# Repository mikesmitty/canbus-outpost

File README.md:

# canbus-outpost

An [LCC](https://openlcb.org/) (OpenLCB) node for model railroads, built around the RP2350. One board:

- drives four servo switch machines, with frog outputs and fascia toggles
- detects RailCom decoders on four track blocks, reporting occupancy and locomotives
- drives up to 16 signal heads on an SSSB chain
- bridges the CAN bus to a host over USB GridConnect
- takes firmware upgrades over LCC

Everything is set through the node's LCC configuration, so it works with any LCC configuration tool. Signals beyond simple links need a host, such as [Interlock](https://github.com/mikesmitty/interlock).

The hardware is in `hardware/canbus-outpost/`, and a one-head signal board is in `hardware/sssb-single/` (both KiCad), each with gerbers, BOM and pick-and-place files in `production/`.

## Signal heads

> [!NOTE]
> The signal chain hasn't been run on hardware yet; so far the firmware has only passed host tests. Boards made before commit 7316e79 have no LED header, but can use a servo output instead: see [Boards without an LED header](#boards-without-an-led-header).

The board speaks [RR-CirKits](https://www.rr-cirkits.com/)' Simple Serial Signal Bus (SSSB) on the LED header: one WS2811 chip per head, daisy-chained with Futaba J servo cables. The LED header supplies 5 V through a 750 mA fuse. Head 1 is the first on the cable unless its **Chain Position** says otherwise, and every chip has to be connected for the ones after it to work, in use or not. WS2811 outputs only sink current, so heads need common-anode LEDs.

### Setting up a head

Heads start disabled, since the board can't tell which are fitted. Under **Signal Heads** in the configuration:

1. Set **Chain Speed** to match the chips' SET pin: 800 kHz when open, 400 kHz when tied to power. RR-CirKits' heads leave it open, so they run at the default of 800 kHz.
2. Set the head's **Enabled**.
3. Set the lamp on each output: **R Lamp**, **Y Lamp** and **G Lamp**, named as on an SSSB head's RGY header. The defaults are red on R, yellow on Y and green on G, which is the SSSB wiring, but any lamp can go on any output. Each output also has its own brightness.
4. Optionally, set **Lamp Fade** to Incandescent. The lamps then warm up over 150 ms and cool down over 300 ms, like ballasted bulbs, instead of switching at once. Flashing aspects fade too.
5. Optionally, set the **Flash Rate** for its flashing aspects: slow (40 a minute), medium (60, the default) or fast (90). Each output also has a **Phase**: phase B lamps light while phase A lamps are dark, so two red lamps can alternate like a crossing flasher, on one head or on two at the same rate.

To add a chip partway along the chain, set the **Chain Position** of each head after it to one more than its number, instead of setting those heads up again on their new numbers. 0, the default, means the head's own number. Two heads on one chip both show on it.

Each aspect has its own event, and only the aspects a head has lamps for are on the bus:

| Aspect | Shows |
| --- | --- |
| Dark | nothing |
| Red, Yellow, Green | that lamp |
| Flashing Red, Yellow, Green | that lamp, at the head's Flash Rate and in each output's Phase, with heads at one rate in step |
| Lunar | a lunar lamp |
| S, D, Number | the lit letters and speed number of NYC subway time signals |

A head lights one kind of lamp at a time, so a light that shows alongside another, like lunar under a red, takes a chip of its own: for example head 1 as red/yellow/green and head 2 as lunar/S/D.

### Lamps of their own

An output set to **Own Events** isn't part of the aspects. It has an On and an Off event of its own, under **Own Events** at the end of **Signal Heads**, and lights at its brightness, fading if the head fades. Use it for panel lights, building lights, or lamps that must light together on one chip. Its events are on the bus while its head is enabled, and it starts out dark. A head whose outputs are all Own Events or None has no aspects on the bus, not even Dark.

### Boards without an LED header

On boards made before the LED header, a servo output can carry the chain:

1. Buffer the data line to 5 V. The servo outputs come straight from the RP2350 at 3.3 V, short of the 3.5 V a WS2811 on 5 V needs for a high. A 74AHCT125-family buffer powered from the servo header's 5 V does it, followed by a 33 Ω resistor as on the LED header. MOSFET level shifters of the kind sold for I2C are too slow at 800 kHz. The [head board](#head-board) can carry the buffer itself.
2. Set **Connected To** under **Signal Heads** to that servo. Its switch machine is then out of use, as if disabled, and the other three work as usual.

The servo header's 5 V comes straight from the board's regulator, without the LED header's 750 mA fuse, so put a fuse in the adapter.

### Head board

`hardware/sssb-single/` is a board for one head: a WS2811 with IN and OUT headers for the chain and an RGY header for a common-anode head. IN and OUT are S, +, − in servo cable order, the same as the LED header, and RGY is 5V, R, G, Y. SET is open, so it runs at 800 kHz. It hasn't been built yet.

It's assembled one of two ways:

- **R1 fitted** (the default): for a head fed by the LED header or another head.
- **U1 and C2 fitted, R1 left off**: the head buffers its own input to 5 V, so it can be the first head on a servo output. U1 is a 74AHCT1G125.

Never fit U1 and R1 together: U1's 5 V output would drive back into the pin feeding the chain. The board has no fuse, so on a servo output put one in the cable.

### Checking the chain

**Signal Test**, at the end of **Signal Heads**, has a Start and a Stop event. From Start until Stop, every chip on the chain, set up or not, lights red, yellow and green in turn and then none, a second each (outputs R, Y and G, as SSSB heads are wired). The heads still follow their events meanwhile, and go back to their aspects at Stop. Each node has its own pair by default; give every node the same pair to test all the chains on the layout at once.

On the USB console, `lights test` does the same until `lights test` again, and `lights <chip> <r> <y> <g>` sets one chip's red, yellow and green directly until the application next updates that chip, ending any test. Chips count from 0 here.

### What to expect from a host

The node has no signal logic. A head shows the last aspect event it received.

- **Simple cases need no host.** An aspect can use the same event ID as a single input, like a turnout's feedback event. Anything that depends on occupancy, routes or the next signal needs a host to decide and send the aspects.
- **A signal with two heads takes one event per head.** Each aspect holds one event ID, so a single event for a whole indication, like red over lunar, only works on a one-chip signal. Two indications that both show red would need two IDs on the same aspect.
- **Heads that always match can share event IDs.** Share all of them or none, or a host that reads a head's state back can mistake one head's aspect for the other's.
- **A reset puts a head on its Power-On Aspect** until the host sends it another.
- **A head doesn't announce changes.** It answers an event identify with the aspect it's showing.

## Building

You'll need CMake, Ninja, `arm-none-eabi-gcc` and `picotool`, the Pico SDK 2.2.0 at `~/.pico-sdk/sdk/2.2.0/`, and FreeRTOS-Kernel at `FREERTOS_KERNEL_PATH`.

```bash
make                  # build the firmware
make flash            # build and load it with picotool
make test             # run the host tests; no hardware needed
```

Once per board, in BOOTSEL mode, install the A/B partition table that LCC firmware upgrades need. It keeps the saved configuration and node ID in the top 64 KB of flash:

```bash
make partition-table
```

A running board goes into BOOTSEL mode without its button through `picotool reboot -f -u` over USB.

Flash with picotool rather than SWD, since loading over SWD replaces the partition table.

Boards set up before the top 64 KB was kept clear have partition B running up to the last 16 KB. They keep working and keep their configuration, but can save only 4 KB of it until they get the new table, which the firmware reports on the debug log at startup. Installing it moves the configuration across on its next save.

## Node ID

Set each board's ID from your OpenLCB-assigned range on the USB console:

```
nodeid 05.01.01.01.12.34
```

Until then the board uses a locally allocated stand-in with an `0A` prefix, made from the chip's device ID.

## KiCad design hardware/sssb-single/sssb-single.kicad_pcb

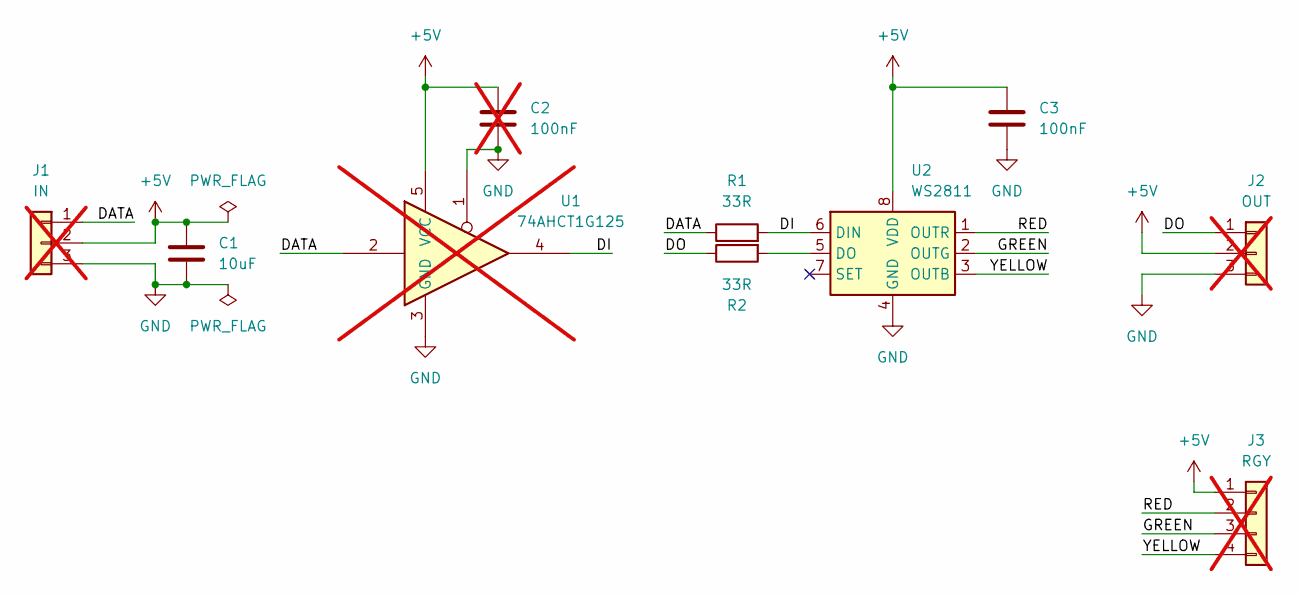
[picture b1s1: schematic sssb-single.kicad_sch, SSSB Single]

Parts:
C1: 10uF; C_0805_2012Metric; LCSC C15850
C2: 100nF; C_0805_2012Metric; LCSC C49678; not fitted
C3: 100nF; C_0805_2012Metric; LCSC C49678
J1: IN; PinHeader_1x03_P2.54mm_Vertical; not fitted
J2: OUT; PinHeader_1x03_P2.54mm_Vertical; not fitted
J3: RGY; PinHeader_1x04_P2.54mm_Vertical; not fitted
R1, R2: 33R; R_0805_2012Metric; LCSC C17634
U1: 74AHCT1G125; SOT-23-5; not fitted
U2: WS2811; SOIC-8_3.9x4.9mm_P1.27mm; LCSC C114581

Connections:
+5V: C1.1, C2.1, C3.1, J1.2, J2.2, J3.1, U1.5 (VCC), U2.8 (VDD)
/DATA: J1.1, R1.1, U1.2
/DI: R1.2, U1.4, U2.6 (DIN)
/DO: J2.1, R2.1
/GREEN: J3.3, U2.2 (OUTG)
/RED: J3.2, U2.1 (OUTR)
/YELLOW: J3.4, U2.3 (OUTB)
GND: C1.2, C2.2, C3.2, J1.3, J2.3, U1.1, U1.3 (GND), U2.4 (GND)
unnamed: R2.2, U2.5 (DO)

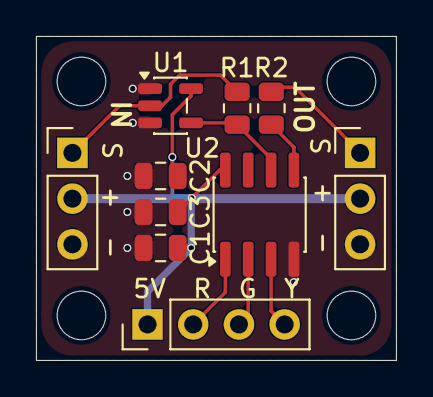
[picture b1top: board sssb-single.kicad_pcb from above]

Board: 2 copper layers, 20.0 x 18.0 mm, 10 parts (0 on the bottom side), 9 nets.

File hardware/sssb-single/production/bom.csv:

Comment,Designator,Footprint,LCSC
100nF,C3,Capacitor_SMD:C_0805_2012Metric,C49678
33R,"R1,R2",Resistor_SMD:R_0805_2012Metric,C17634
10uF,C1,Capacitor_SMD:C_0805_2012Metric,C15850
WS2811,U2,Package_SO:SOIC-8_3.9x4.9mm_P1.27mm,C114581

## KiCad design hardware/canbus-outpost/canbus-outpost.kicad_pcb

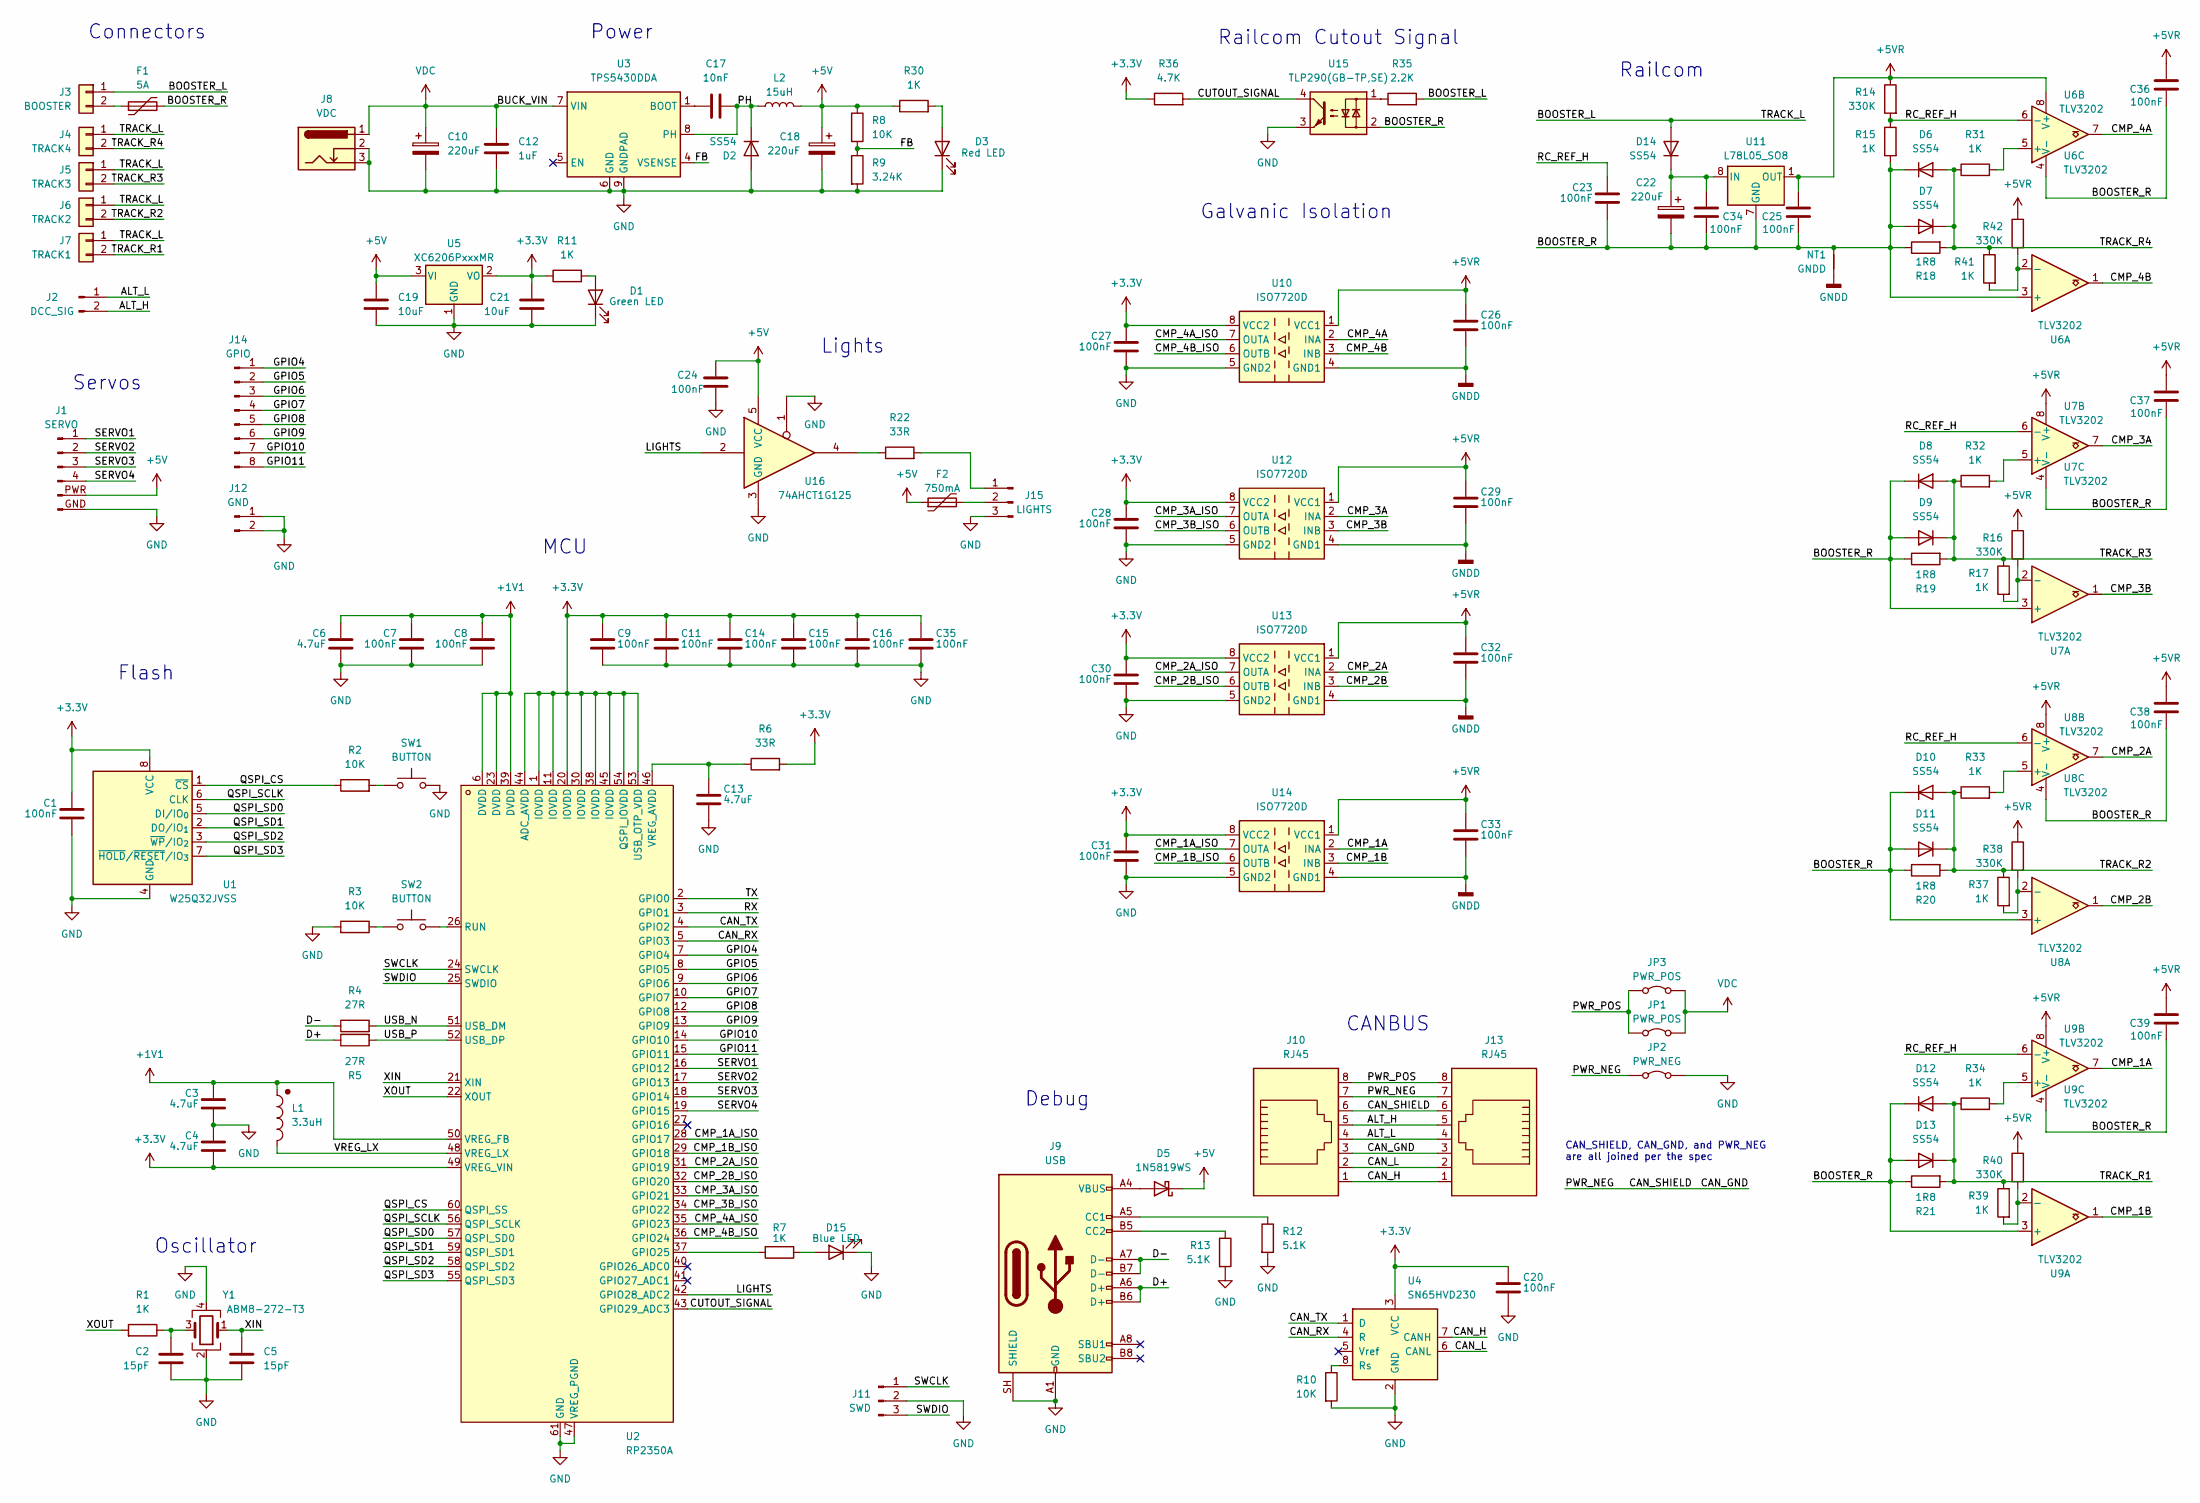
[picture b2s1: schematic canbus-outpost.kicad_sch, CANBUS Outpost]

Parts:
C1, C7, C8, C9, C11, C14, C15, C16, C20, C23, C24, C25, C26, C27, C28, C29, C30, C31, C32, C33, C34, C35, C36, C37, C38, C39: 100nF; C_0402_1005Metric; LCSC C1525
C2, C5: 15pF; C_0402_1005Metric; LCSC C1548
C3, C4: 4.7uF; C_0402_1005Metric_small_pads; LCSC C23733
C6, C13: 4.7uF; C_0402_1005Metric; LCSC C23733
C10, C18, C22: 220uF; CP_Elec_6.3x7.7; LCSC C7471881
C12: 1uF; C_0603_1608Metric; LCSC C15849
C17: 10nF; C_0402_1005Metric; LCSC C15195
C19, C21: 10uF; C_0805_2012Metric; LCSC C15850
D1: Green LED; LED_0603_1608Metric; LCSC C965804
D2, D6, D7, D8, D9, D10, D11, D12, D13, D14: SS54; D_SMA; LCSC C22452
D3: Red LED; LED_0603_1608Metric; LCSC C2286
D5: 1N5819WS; D_SOD-323; LCSC C191023
D15: Blue LED; LED_0603_1608Metric; LCSC C965807
F1: 5A; Fuse_2920_7451Metric; LCSC C20539728
F2: 750mA; Fuse_1206_3216Metric; LCSC C2830242
J1: SERVO; ServoHeader_3x04_2.54mm
J2: DCC_SIG; JST_XH_S2B-XH-A_1x02_P2.50mm_Horizontal
J3: BOOSTER; PhoenixContact_MC_1,5_2-G-3.5_1x02_P3.50mm_Horizontal
J4: TRACK4; PhoenixContact_MC_1,5_2-G-3.5_1x02_P3.50mm_Horizontal
J5: TRACK3; PhoenixContact_MC_1,5_2-G-3.5_1x02_P3.50mm_Horizontal
J6: TRACK2; PhoenixContact_MC_1,5_2-G-3.5_1x02_P3.50mm_Horizontal
J7: TRACK1; PhoenixContact_MC_1,5_2-G-3.5_1x02_P3.50mm_Horizontal
J8: VDC; BarrelJack_Wuerth_694106106102_2.0x5.5mm; LCSC C319134
J9: USB; USB_C_Receptacle_GCT_USB4115-03-C; LCSC C720628
J10, J13: RJ45; RJ45_Amphenol_54602-x08_Horizontal; LCSC C3000197
J11: SWD; PinHeader_1x03_P2.54mm_Vertical
J12: GND; PinHeader_1x02_P2.54mm_Vertical
J14: GPIO; PinHeader_1x08_P2.54mm_Vertical
J15: LIGHTS; PinHeader_1x03_P2.54mm_Vertical
JP1: PWR_POS; PinHeader_1x02_P2.54mm_Vertical
JP2: PWR_NEG; SolderJumper-2_P1.3mm_Bridged_Pad1.0x1.5mm
JP3: PWR_POS; SolderJumper-2_P1.3mm_Bridged_Pad1.0x1.5mm
L1: 3.3uH; L_pol_2016; LCSC C42411119
L2: 15uH; L_Changjiang_FXL0630; LCSC C177243
NT1: GNDD; NetTie-2_SMD_Pad0.5mm
R1, R7, R11, R15, R17, R30, R31, R32, R33, R34, R37, R39, R41: 1K; R_0402_1005Metric; LCSC C11702
R2, R3, R8, R10: 10K; R_0402_1005Metric; LCSC C25744
R4, R5: 27R; R_0402_1005Metric; LCSC C25100
R6, R22: 33R; R_0402_1005Metric; LCSC C25105
R9: 3.24K; R_0402_1005Metric; LCSC C11457
R12, R13: 5.1K; R_0402_1005Metric; LCSC C25905
R14, R16, R38, R40, R42: 330K; R_0402_1005Metric; LCSC C25778
R18, R19, R20, R21: 1R8; R_1206_3216Metric; LCSC C15545
R35: 2.2K; R_1206_3216Metric; LCSC C17948
R36: 4.7K; R_0402_1005Metric; LCSC C25900
SW1, SW2: BUTTON; SW_SPST_PTS810; LCSC C139797
U1: W25Q32JVSS; SOIC-8_5.3x5.3mm_P1.27mm; LCSC C179173
U2: RP2350A; QFN-60-1EP_7x7mm_P0.4mm_EP3.4x3.4mm; LCSC C42411118
U3: TPS5430DDA; TI_SO-PowerPAD-8_ThermalVias; LCSC C9864
U4: SN65HVD230; SOIC-8_3.9x4.9mm_P1.27mm; LCSC C12084
U5: XC6206PxxxMR; SOT-23-3; LCSC C5446
U6, U7, U8, U9: TLV3202; SOIC-8_3.9x4.9mm_P1.27mm; LCSC C129325
U10, U12, U13, U14: ISO7720D; SOIC-8_3.9x4.9mm_P1.27mm; LCSC C486037
U11: L78L05_SO8; SOIC-8_3.9x4.9mm_P1.27mm; LCSC C7543
U15: TLP290(GB-TP,SE); SOIC-4_4.55x2.6mm_P1.27mm; LCSC C73839
U16: 74AHCT1G125; SOT-23-5; LCSC C7484
Y1: ABM8-272-T3; Crystal_SMD_3225-4Pin_3.2x2.5mm; LCSC C20625731

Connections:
+1V1: C3.1, C6.1, C7.1, C8.1, L1.1, U2.6 (DVDD), U2.23 (DVDD), U2.39 (DVDD), U2.50 (VREG_FB)
+3.3V: C1.1, C4.2, C9.1, C11.1, C14.1, C15.1, C16.1, C20.1, C21.1, C27.1, C28.1, C30.1, C31.1, C35.1, R6.2, R11.1, R36.1, U1.8 (VCC), U2.1 (IOVDD), U2.11 (IOVDD), U2.20 (IOVDD), U2.30 (IOVDD), U2.38 (IOVDD), U2.44 (ADC_AVDD), U2.45 (IOVDD), U2.49 (VREG_VIN), U2.53 (USB_OTP_VDD), U2.54 (QSPI_IOVDD), U4.3 (VCC), U5.2 (VO), U10.8 (VCC2), U12.8 (VCC2), U13.8 (VCC2), U14.8 (VCC2)
+5V: C18.1, C19.1, C24.1, D5.1 (K), F2.1, J1.PWR (Pin_5), L2.2, R8.1, R30.1, U5.3 (VI), U16.5 (VCC)
+5VR: C25.1, C26.1, C29.1, C32.1, C33.1, C36.1, C37.1, C38.1, C39.1, R14.1, R16.1, R38.1, R40.1, R42.1, U6.8 (V+), U7.8 (V+), U8.8 (V+), U9.8 (V+), U10.1 (VCC1), U11.1 (OUT), U12.1 (VCC1), U13.1 (VCC1), U14.1 (VCC1)
/ALT_H: J2.2, J10.5, J13.5
/ALT_L: J2.1, J10.4, J13.4
/BOOSTER_L: D14.2 (A), J3.1, J4.1, J5.1, J6.1, J7.1, R35.2
/BOOSTER_R: C22.2, C23.2, C25.2, C34.2, C36.2, C37.2, C38.2, C39.2, D6.1 (K), D7.2 (A), D8.1 (K), D9.2 (A), D10.1 (K), D11.2 (A), D12.1 (K), D13.2 (A), F1.2, NT1.2, R15.2, R18.1, R19.1, R20.1, R21.1, U6.3 (+), U6.4 (V-), U7.3 (+), U7.4 (V-), U8.3 (+), U8.4 (V-), U9.3 (+), U9.4 (V-), U11.2 (GND), U11.3 (GND), U11.6 (GND), U11.7 (GND), U15.2
/CAN_GND: J10.3, J10.6, J10.7, J13.3, J13.6, J13.7, JP2.1 (A)
/CAN_H: J10.1, J13.1, U4.7 (CANH)
/CAN_L: J10.2, J13.2, U4.6 (CANL)
/CAN_RX: U2.5 (GPIO3), U4.4 (R)
/CAN_TX: U2.4 (GPIO2), U4.1 (D)
/CMP_1A: U9.7, U14.2 (INA)
/CMP_1A_ISO: U2.28 (GPIO17), U14.7 (OUTA)
/CMP_1B: U9.1, U14.3 (INB)
/CMP_1B_ISO: U2.29 (GPIO18), U14.6 (OUTB)
/CMP_2A: U8.7, U13.2 (INA)
/CMP_2A_ISO: U2.31 (GPIO19), U13.7 (OUTA)
/CMP_2B: U8.1, U13.3 (INB)
/CMP_2B_ISO: U2.32 (GPIO20), U13.6 (OUTB)
/CMP_3A: U7.7, U12.2 (INA)
/CMP_3A_ISO: U2.33 (GPIO21), U12.7 (OUTA)
/CMP_3B: U7.1, U12.3 (INB)
/CMP_3B_ISO: U2.34 (GPIO22), U12.6 (OUTB)
/CMP_4A: U6.7, U10.2 (INA)
/CMP_4A_ISO: U2.35 (GPIO23), U10.7 (OUTA)
/CMP_4B: U6.1, U10.3 (INB)
/CMP_4B_ISO: U2.36 (GPIO24), U10.6 (OUTB)
/CUTOUT_SIGNAL: R36.2, U2.43 (GPIO29_ADC3), U15.4
/D+: J9.A6 (D+), J9.B6 (D+), R5.1
/D-: J9.A7 (D-), J9.B7 (D-), R4.1
/FB: R8.2, R9.1, U3.4 (VSENSE)
/GPIO4: J14.1, U2.7 (GPIO4)
/GPIO5: J14.2, U2.8 (GPIO5)
/GPIO6: J14.3, U2.9 (GPIO6)
/GPIO7: J14.4, U2.10 (GPIO7)
/GPIO8: J14.5, U2.12 (GPIO8)
/GPIO9: J14.6, U2.13 (GPIO9)
/GPIO10: J14.7, U2.14 (GPIO10)
/GPIO11: J14.8, U2.15 (GPIO11)
/LIGHTS: U2.42 (GPIO28_ADC2), U16.2
/PH: C17.2, D2.1 (K), L2.1, U3.8 (PH)
/PWR_POS: J10.8, J13.8, JP1.1 (A), JP3.1 (A)
/QSPI_CS: R2.1, U1.1 (~CS), U2.60 (QSPI_SS)
/QSPI_SCLK: U1.6 (CLK), U2.56 (QSPI_SCLK)
/QSPI_SD0: U1.5 (DI/IO_{0}), U2.57 (QSPI_SD0)
/QSPI_SD1: U1.2 (DO/IO_{1}), U2.59 (QSPI_SD1)
/QSPI_SD2: U1.3 (~WP/IO_{2}), U2.58 (QSPI_SD2)
/QSPI_SD3: U1.7 (~HOLD/~RESET/IO_{3}), U2.55 (QSPI_SD3)
/RC_REF_H: C23.1, R14.2, R15.1, U6.6 (-), U7.6 (-), U8.6 (-), U9.6 (-)
/RX: U2.3 (GPIO1)
/SERVO1: J1.1, U2.16 (GPIO12)
/SERVO2: J1.2, U2.17 (GPIO13)
/SERVO3: J1.3, U2.18 (GPIO14)
/SERVO4: J1.4, U2.19 (GPIO15)
/SWCLK: J11.1, U2.24 (SWCLK)
/SWDIO: J11.3, U2.25 (SWDIO)
/TRACK_R1: D12.2 (A), D13.1 (K), J7.2, R21.2, R34.1, R39.1
/TRACK_R2: D10.2 (A), D11.1 (K), J6.2, R20.2, R33.1, R37.1
/TRACK_R3: D8.2 (A), D9.1 (K), J5.2, R17.1, R19.2, R32.1
/TRACK_R4: D6.2 (A), D7.1 (K), J4.2, R18.2, R31.1, R41.1
/TX: U2.2 (GPIO0)
/USB_N: R4.2, U2.51 (USB_DM)
/USB_P: R5.2, U2.52 (USB_DP)
/VREG_LX: L1.2, U2.48 (VREG_LX)
/XIN: C5.1, U2.21 (XIN), Y1.1
/XOUT: R1.2, U2.22 (XOUT)
GND: C1.2, C2.2, C3.2, C4.1, C5.2, C6.2, C7.2, C8.2, C9.2, C10.2, C11.2, C12.2, C13.2, C14.2, C15.2, C16.2, C18.2, C19.2, C20.2, C21.2, C24.2, C27.2, C28.2, C30.2, C31.2, C35.2, D1.1 (K), D2.2 (A), D3.1 (K), D15.1 (K), J1.GND (Pin_6), J8.2, J8.3, J9.A1 (GND), J9.A12 (GND), J9.B1 (GND), J9.B12 (GND), J9.SH (SHIELD), J11.2, J12.1, J12.2, J15.3, JP2.2 (B), R3.2, R9.2, R10.2, R12.2, R13.2, SW1.2, U1.4 (GND), U2.47 (VREG_PGND), U2.61 (GND), U3.6 (GND), U3.9 (GNDPAD), U4.2 (GND), U5.1 (GND), U10.5 (GND2), U12.5 (GND2), U13.5 (GND2), U14.5 (GND2), U15.3, U16.1, U16.3 (GND), Y1.2, Y1.4
GNDD: C26.2, C29.2, C32.2, C33.2, NT1.1, U10.4 (GND1), U12.4 (GND1), U13.4 (GND1), U14.4 (GND1)
unnamed: C2.1, R1.1, Y1.3
unnamed: D1.2 (A), R11.2
unnamed: D3.2 (A), R30.2
unnamed: D5.2 (A), J9.A4 (VBUS), J9.A9 (VBUS), J9.B4 (VBUS), J9.B9 (VBUS)
unnamed: C22.1, C34.1, D14.1 (K), U11.8 (IN)
unnamed: D15.2 (A), R7.1
unnamed: F1.1, J3.2
unnamed: J9.A5 (CC1), R12.1
unnamed: J9.B5 (CC2), R13.1
unnamed: J15.1, R22.2
unnamed: F2.2, J15.2
unnamed: R2.2, SW1.1
unnamed: R3.1, SW2.2
unnamed: R22.1, U16.4
unnamed: R35.1, U15.1
unnamed: R7.2, U2.37 (GPIO25)
unnamed: SW2.1, U2.26 (RUN)
unnamed: C13.1, R6.1, U2.46 (VREG_AVDD)
unnamed: C17.1, U3.1 (BOOT)
unnamed: R10.1, U4.8 (Rs)
unnamed: R41.2, R42.2, U6.2 (-)
unnamed: R31.2, U6.5 (+)
unnamed: R16.2, R17.2, U7.2 (-)
unnamed: R32.2, U7.5 (+)
unnamed: R37.2, R38.2, U8.2 (-)
unnamed: R33.2, U8.5 (+)
unnamed: R39.2, R40.2, U9.2 (-)
unnamed: R34.2, U9.5 (+)
VDC: C10.1, C12.1, J8.1, JP1.2 (B), JP3.2 (B), U3.7 (VIN)

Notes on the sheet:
Oscillator
Lights
Railcom
CAN_SHIELD, CAN_GND, and PWR_NEG are all joined per the spec
Galvanic Isolation
MCU
Railcom Cutout Signal
Debug
Servos
Flash
Connectors
Power
CANBUS

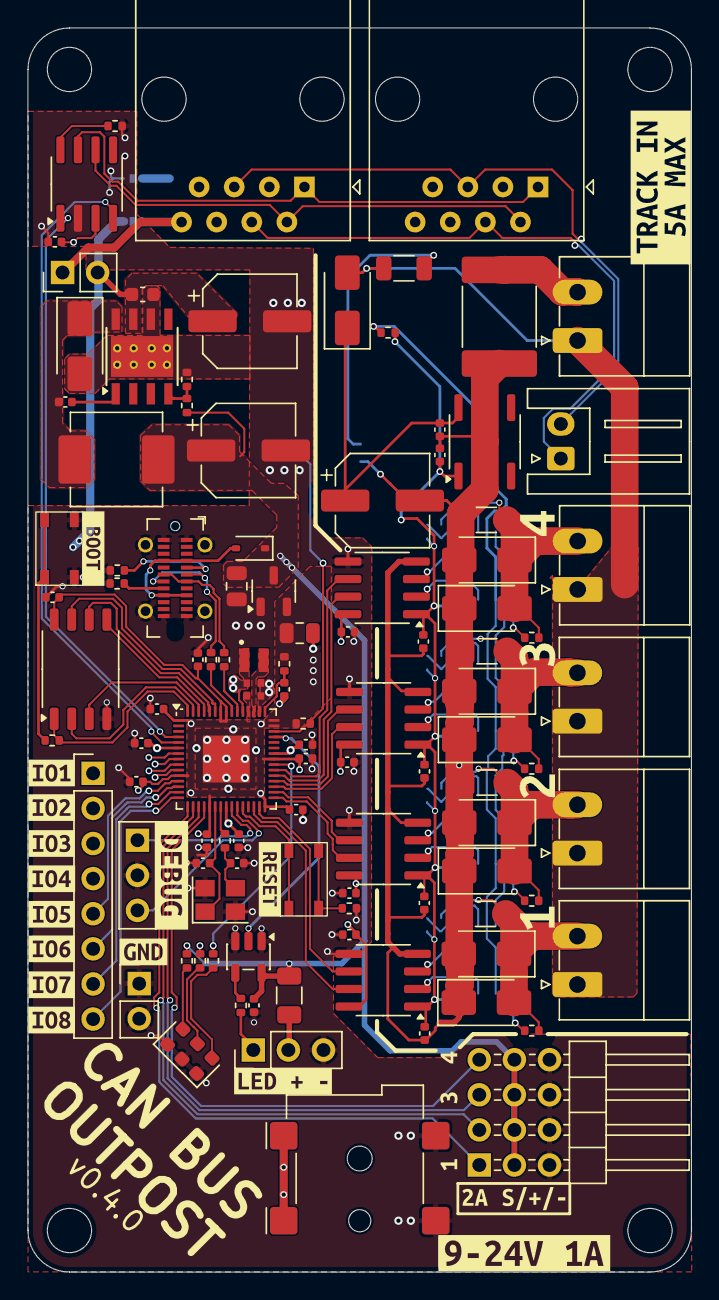
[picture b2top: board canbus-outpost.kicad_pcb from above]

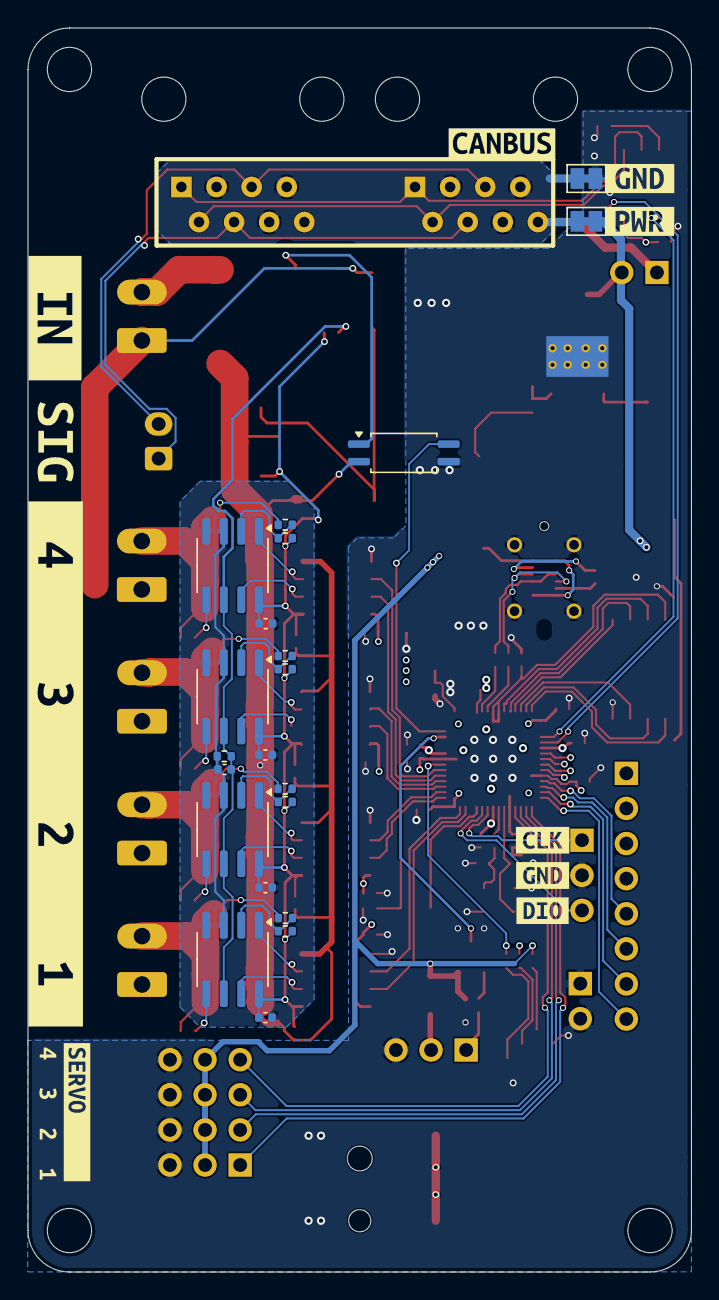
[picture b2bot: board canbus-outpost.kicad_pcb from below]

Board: 4 copper layers, 48.0 x 90.0 mm, 162 parts (32 on the bottom side), 97 nets.

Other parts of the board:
kibuzzard-6AE53D03: G***; kibuzzard-6AE53D03
kibuzzard-6AE558B7: G***; kibuzzard-6AE558B7
kibuzzard-69DC4DF3: G***; kibuzzard-69DC4DF3
kibuzzard-69DC4DFC: G***; kibuzzard-69DC4DFC
kibuzzard-69DC4E0F: G***; kibuzzard-69DC4E0F
kibuzzard-69DC4E03: G***; kibuzzard-69DC4E03
kibuzzard-69DC490B: G***; kibuzzard-69DC490B
kibuzzard-69DC492A: G***; kibuzzard-69DC492A
kibuzzard-69DC4912: G***; kibuzzard-69DC4912
kibuzzard-69DC4921: G***; kibuzzard-69DC4921
kibuzzard-688B6E49: G***; kibuzzard-688B6E49
kibuzzard-688B6E90: G***; kibuzzard-688B6E90
kibuzzard-688B7D39: G***; kibuzzard-688B7D39
kibuzzard-688B72C3: G***; kibuzzard-688B72C3
kibuzzard-688B73DB: G***; kibuzzard-688B73DB
kibuzzard-688B7055: G***; kibuzzard-688B7055
kibuzzard-688B7428: G***; kibuzzard-688B7428
kibuzzard-688B7622: G***; kibuzzard-688B7622
kibuzzard-688B7949: G***; kibuzzard-688B7949
kibuzzard-688BEB22: G***; kibuzzard-688BEB22
kibuzzard-688BEC68: G***; kibuzzard-688BEC68
kibuzzard-688BEEB4: G***; kibuzzard-688BEEB4
kibuzzard-688BF0B8: G***; kibuzzard-688BF0B8
kibuzzard-688BF0BD: G***; kibuzzard-688BF0BD
kibuzzard-688D2D9A: G***; kibuzzard-688D2D9A
kibuzzard-688D2D45: G***; kibuzzard-688D2D45
kibuzzard-688D2DB6: G***; kibuzzard-688D2DB6
kibuzzard-688D2DD7: G***; kibuzzard-688D2DD7
kibuzzard-688D2F72: G***; kibuzzard-688D2F72
kibuzzard-688D2FE4: G***; kibuzzard-688D2FE4
kibuzzard-688D37AD: G***; kibuzzard-688D37AD
kibuzzard-688D3063: G***; kibuzzard-688D3063

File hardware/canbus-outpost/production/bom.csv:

Comment,Designator,Footprint,LCSC
SS54,"D2,D6,D7,D8,D9,D10,D11,D12,D13,D14",Library:D_SMA,C22452
TLV3202,"U6,U7,U8,U9",Library:SOIC-8_3.9x4.9mm_P1.27mm,C129325
100nF,"C1,C7,C8,C9,C11,C14,C15,C16,C20,C23,C25,C26,C27,C28,C29,C30,C31,C32,C33,C34,C35,C36,C37,C38,C39",Library:C_0402_1005Metric,C1525
ISO7720D,"U10,U12,U13,U14",Package_SO:SOIC-8_3.9x4.9mm_P1.27mm,C486037
1R8,"R18,R19,R20,R21",Library:R_1206_3216Metric,C15545
Green LED,D1,Library:LED_0603_1608Metric,C965804
SERVO,J1,Library:ServoHeader_3x04_2.54mm,
USB,J9,Library:PinHeader_1x04_P2.54mm_Vertical,
10K,"R2,R3,R8,R10",Library:R_0402_1005Metric,C25744
15pF,"C2,C5",Library:C_0402_1005Metric,C1548
SN65HVD230,U4,Library:SOIC-8_3.9x4.9mm_P1.27mm,C12084
Blue LED,D15,Library:LED_0603_1608Metric,C965807
1K,"R1,R7,R11,R15,R17,R30,R31,R32,R33,R34,R37,R39,R41",Library:R_0402_1005Metric,C11702
W25Q32JVSS,U1,Library:SOIC-8_5.3x5.3mm_P1.27mm,C82344
1uF,C12,Library:C_0603_1608Metric,C15849
3.24K,R9,Library:R_0402_1005Metric,C11457
330K,"R14,R16,R38,R40,R42",Library:R_0402_1005Metric,C25778
EL3H4(A)(TA)-G,U15,Package_SO:SOIC-4_4.55x2.6mm_P1.27mm,C42384998
BUTTON,"SW1,SW2",Library:SW_SPST_PTS810,C139797
220uF,"C10,C18,C22",Library:CP_Elec_6.3x7.7,C7471881
GPIO,J14,Connector_PinHeader_2.54mm:PinHeader_1x08_P2.54mm_Vertical,
L78L05_SO8,U11,Package_SO:SOIC-8_3.9x4.9mm_P1.27mm,C7543
3.3uH,L1,Library:L_pol_2016,C42411119
4.7uF,"C3,C4",Library:C_0402_1005Metric_small_pads,C23733
27R,"R4,R5",Library:R_0402_1005Metric,C25100
RJ45,"J10,J13",Library:RJ45_Amphenol_54602-x08_Horizontal,C3000197
RP2350A,U2,Library:QFN-60-1EP_7x7mm_P0.4mm_EP3.4x3.4mm,C42411118
BOOSTER,J3,"Library:PhoenixContact_MC_1,5_2-G-3.5_1x02_P3.50mm_Horizontal",
10uF,"C19,C21",Library:C_0805_2012Metric,C15850
4.7uF,"C6,C13",Library:C_0402_1005Metric,C23733
VDC,J8,Library:BarrelJack_Wuerth_694106106102_2.0x5.5mm,C319134
DCC_SIG,J2,Library:JST_XH_S2B-XH-A_1x02_P2.50mm_Horizontal,
4.7K,R36,Library:R_0402_1005Metric,C25900
ABM8-272-T3,Y1,Library:Crystal_SMD_3225-4Pin_3.2x2.5mm,C20625731
5A,F1,Library:Fuse_2920_7451Metric,C20539728
TRACK2,J6,"Library:PhoenixContact_MC_1,5_2-G-3.5_1x02_P3.50mm_Horizontal",
PWR_POS,JP3,Jumper:SolderJumper-2_P1.3mm_Bridged_Pad1.0x1.5mm,
XC6206PxxxMR,U5,Library:SOT-23-3,C5446
TRACK3,J5,"Library:PhoenixContact_MC_1,5_2-G-3.5_1x02_P3.50mm_Horizontal",
PWR_POS,JP1,Connector_PinHeader_2.54mm:PinHeader_1x02_P2.54mm_Vertical,
10nF,C17,Library:C_0402_1005Metric,C15195
1N5819WS,D5,Diode_SMD:D_SOD-323,C191023
2.2K,R35,Library:R_1206_3216Metric,C17948
15uH,L2,Library:L_Changjiang_FXL0630,C177243
TRACK1,J7,"Library:PhoenixContact_MC_1,5_2-G-3.5_1x02_P3.50mm_Horizontal",
TPS5430DDA,U3,Library:TI_SO-PowerPAD-8_ThermalVias,C9864
33R,R6,Library:R_0402_1005Metric,C25105
Red LED,D3,Library:LED_0603_1608Metric,C2286
SWD,J11,Library:PinHeader_1x03_P2.54mm_Vertical,
TRACK4,J4,"Library:PhoenixContact_MC_1,5_2-G-3.5_1x02_P3.50mm_Horizontal",
PWR_NEG,JP2,Jumper:SolderJumper-2_P1.3mm_Bridged_Pad1.0x1.5mm,

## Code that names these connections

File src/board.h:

#ifndef BOARD_H
#define BOARD_H

#include "pico/stdlib.h"

// Debug UART0
#define DEBUG_UART uart0
#define DEBUG_TX_PIN 0
#define DEBUG_RX_PIN 1

// CAN Bus (PIO)
#define CAN_TX_PIN 2
#define CAN_RX_PIN 3

// General Purpose I/O
#define GPIO_OUT1 4
#define GPIO_OUT2 5
#define GPIO_OUT3 6
#define GPIO_OUT4 7

#define GPIO_IN1 8
#define GPIO_IN2 9
#define GPIO_IN3 10
#define GPIO_IN4 11

// Servo PWM Outputs
#define SERVO1_PIN 12
#define SERVO2_PIN 13
#define SERVO3_PIN 14
#define SERVO4_PIN 15

// RailCom Detector Channels (A and B for Data/Orientation)
// Channel n is the TRACK_Rn block. A is high while current flows from the
// rail into BOOSTER_R, B while it flows the other way; both low when idle.
#define RC_CH1_A 17
#define RC_CH1_B 18
#define RC_CH2_A 19
#define RC_CH2_B 20
#define RC_CH3_A 21
#define RC_CH3_B 22
#define RC_CH4_A 23
#define RC_CH4_B 24

// RailCom cutout: high while the booster holds the cutout (U15 opto)
#define RC_CUTOUT_PIN 29

// The RailCom PIO samples 16 consecutive GPIOs starting here; all RC_* pins
// must fall within that range.
#define RC_SAMPLE_BASE_PIN 17

// Signal lights: a WS2811 chain on the LED header (J15)
#define LIGHTS_PIN 28

// Board identify LED
#ifndef PICO_DEFAULT_LED_PIN
#define IDENTIFY_LED_PIN 25
#else
#define IDENTIFY_LED_PIN PICO_DEFAULT_LED_PIN
#endif

#endif // BOARD_H

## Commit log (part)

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2025-09-01 feat: initial commit
2025-09-01 fix: update part rotations
2026-03-22 chore: update .gitignore
2026-03-29 fix: switch from LM393 to TLV3202 for railcom signals
2026-03-30 feat: add initial firmware implementation for canbus-outpost
    - Initialize C/C++ firmware project for RP2350
    - Integrate OpenLcbCLib and can2040 libraries
    - Add RailCom UART PIO implementation
    - Setup VS Code configuration and CMake build system
2026-03-30 fix: Correct RailCom PIO timing and implement cutout-based gating
    - Adjusted PIO UART loop to exactly 10 cycles per bit.
    - Removed redundant push in PIO (relying on autopush).
    - Implemented cutout synchronization using Pin B for each channel.
    - Added FIFO clearing at the start of the cutout to eliminate DCC noise.
    - Fixed pin assignment confusion (Pin A is Data, Pin B is Cutout).
2026-04-09 feat(ci): add release-please workflow and improve FreeRTOS inclusion
2026-04-09 chore(main): release 0.2.0
2026-04-09 chore(main): release 0.2.0 (#1)
2026-04-10 chore(main): release 0.2.1
2026-04-10 chore(main): release 0.2.1 (#2)
2026-04-10 chore(main): release 0.3.0
2026-04-15 chore(deps): add renovate.json
